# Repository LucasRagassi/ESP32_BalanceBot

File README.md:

# ESP32 BalanceBot V1

Base segura para o BalanceBot de aproximadamente 30 cm, com ESP32 DevKit/WROOM-32 a confirmar, MPU6050, dois motores de passo Creality 42-34 BJ42D15-26V12, cada um com um TMC2209 independente. Estrutura impressa em 3D e PCB KiCad são requisitos do projeto; consulte [CAD_REQUIREMENTS.md](./CAD_REQUIREMENTS.md) e [PCB_REQUIREMENTS.md](./PCB_REQUIREMENTS.md).

**Fase atual: simulação e arquitetura; nenhuma saída STEP/DIR ou driver físico é inicializado ou habilitado.** Valores elétricos dos motores e módulos permanecem pendentes de datasheet/medição. `esp32dev` é só o alvo genérico para compilar e não comprova qual DevKit está conectado.

## Arquitetura

- `include/balance` e `src`: PID de equilíbrio, filtro complementar, estado seguro, validação/persistência NVS, interfaces StepPulseEngine/StepperDriver, rampas de aceleração independentes e monitor de passos perdidos.
- `src/esp32_rmt_step_pulse.cpp`: backend de pulsos RMT para ESP32 isolado por interface. Não é instanciado pelo firmware V1. `src/esp32_app.cpp` usa somente modelos de motor em RAM; o PID de 200 Hz produz demandas limitadas/rampadas simuladas.
- `StepperMotorConfig` de cada lado inclui limite de corrente, sentido, velocidade máxima em steps/s e aceleração em steps/s². Os limites de software são genéricos e conservadores, não substituem o limite seguro do conjunto motor/módulo/PCB.
- A configuração WebSocket é validada na tarefa de controle, aplicada aos simuladores e persistida pela tarefa principal, fora do caminho crítico. Valores de corrente são guardados mas ainda **não são enviados por UART aos TMC2209**.
- A tarefa de controle solicita período de 5 ms, registra execução, jitter, deadlines e desativa os modelos ao entrar em falha. Não faz rede, LittleFS ou NVS.
- Encoders físicos ainda não foram especificados. A perda de passos exibida/testada é exclusivamente simulada; não existe detecção física de posição nesta versão.

## Build e testes

Instale PlatformIO Core e execute na raiz:

```sh
pio run -e native
pio test -e native
pio run -e esp32dev
pio run -e esp32dev -t buildfs
```

Para hardware, somente depois da revisão elétrica e mecânica: `pio run -e esp32dev -t uploadfs`, `pio run -e esp32dev -t upload` e `pio device monitor -b 115200`. Upload físico não foi executado.

Os testes nativos cobrem PID e configuração, estados/falhas, comandos remotos, rampas distintas por eixo, sentido/limites de motor, detecção simulada de passos perdidos e falhas. Build e resultados mais recentes estão em “Validação registrada”.

## Wi-Fi e painel

**Fase 1.4.3 — SoftAP:** `status` agora compara eventos e driver reais (modo/configuração, canal, BSSID, clientes e scans). IP 192.168.4.1 ou sucesso no boot não comprovam beacons RF. Não há restart automático; a causa do desaparecimento em repouso segue dependente de captura física. Veja [DIAGNOSTICO_SOFTAP.md](./DIAGNOSTICO_SOFTAP.md). O scan continua manual/autenticado e exige intervalo mínimo de 15 s.

**Fase 1.4.7 — configuração de rede simplificada:** no Android conectado ao AP `BalanceBot-Setup`, abra `http://192.168.4.1/network`, preencha SSID/senha do roteador **2,4 GHz** e toque **Conectar e salvar**. Não há token, login, cookies ou sessões administrativas. Depois de obter DHCP válido, o ESP32 salva e verifica automaticamente a configuração em NVS `bb_wifi`; falhas preservam a configuração anterior. O portal mostra o IP STA para acesso pelo Fedora na mesma LAN e mantém os campos/foco durante as consultas. O reboot recupera a configuração gravada e reconecta.

**Use somente em rede confiável:** qualquer cliente com acesso ao AP ou à LAN pode consultar/alterar a rede. A senha WPA2 e o IP `192.168.4.1/24` do AP foram preservados. HTTP não cifra a senha STA em trânsito; ela não é devolvida em JSON/telemetria/logs. Não publique as portas 80/81 na Internet. A configuração de rede não concede autorização para acionar motores: DEMO, intertravamentos e motores físicos desabilitados permanecem. Veja [REDE_AP_STA.md](./REDE_AP_STA.md) para arquitetura, testes e limitações.

**Console:** NORMAL continua padrão. Use `pio device monitor -b 115200`, comandos `status`, `help` e `log quiet|normal|debug`. O comando `admin` e a geração/validação de token foram removidos; QR administrativo das fases anteriores não é necessário. Falhas críticas, FAULT e watchdog continuam visíveis.

O link **Diagnóstico** abre `/diagnostics`, uma página responsiva de consulta que atualiza os indicadores a partir da API JSON `/health`. Ela não ocupa a conexão WebSocket do controlador. Seus arquivos `diagnostics.html`, `diagnostics.css` e `diagnostics.js` devem acompanhar o upload manual do LittleFS. Em falhas de consulta, a página sinaliza os dados desatualizados. Consulte [DIAGNOSTICO_HTTP.md](./DIAGNOSTICO_HTTP.md) para testes e instruções de gravação.

Depois de gravar firmware e filesystem, conecte ao AP `BalanceBot-Setup` (senha padrão `BalanceBot123`) e abra `http://192.168.4.1/`. Altere a senha antes de qualquer ensaio. É possível substituir credenciais com `BALANCEBOT_AP_SSID` e `BALANCEBOT_AP_PASSWORD` em `build_flags`.

Para diagnosticar acesso pelo Android, abra primeiro `http://192.168.4.1/health`. Este endpoint não usa LittleFS e retorna JSON com estado do AP/HTTP/WebSocket/tarefa, disponibilidade da IMU, heap e razão de reset. Se LittleFS não estiver montado, `/` ainda responde com uma página HTML curta de diagnóstico; os recursos completos podem exigir `pio run -e esp32dev -t uploadfs`. Prefira digitar o endereço HTTP explícito e desative temporariamente a troca automática para dados móveis/rede sem internet, caso o Android abandone o AP.

O painel expõe perfis independentes por motor. Corrente 0 indica não configurada; configure-a somente após validar corrente de fase/RMS, Rsense e dissipação para os módulos reais. Um cliente WebSocket controlador é aceito; perda de conexão/timeout zera a referência remota, sem desabilitar abruptamente o laço de equilíbrio. A configuração de motor pode ser alterada apenas fora de `EQUILIBRANDO`.

## Estados e segurança

`DESARMADO → CALIBRANDO → PRONTO → EQUILIBRANDO`; falhas latched levam a `FALHA`. Com a MPU6050 ausente no boot, o sistema entra em `DEMO`, permanece servindo a interface e não aceita armamento. A detecção inicial ocorre uma vez; tentativas de recuperação são separadas por 5 s e não há leituras I2C a cada ciclo enquanto o sensor estiver ausente. Se a IMU falhar durante equilíbrio, o controle entra em falha e os modelos são desabilitados. A detecção posterior do sensor não rearma automaticamente: requer reinicialização deliberada. São também tratados atraso de controle, inclinação excessiva, intertravamento aberto e divergência de passos simulada.

**Não conecte motores aos pinos STEP/DIR e não use este firmware para equilibrar fisicamente o robô.** Antes de uma futura habilitação, é obrigatório um E-stop que corte a potência independentemente do software e hardware que mantenha ENN dos dois TMC2209 inativo no boot/reset/brownout. Consulte [HARDWARE.md](./HARDWARE.md).

## Diagnóstico do boot e concorrência

Em 115200 baud, NORMAL exibe um resumo organizado e transições importantes; `status` repete o estado. Em DEBUG, as etapas registram início/resultado, timestamp monotônico, heap e NVS/defaults; o loop e a tarefa produzem diagnósticos de heartbeat/watermark a cada 10 s, impressos pelo loop por filas não bloqueantes. Esses diagnósticos periódicos não aparecem em NORMAL/QUIET. Watermark abaixo de 256 unidades gera alerta crítico em qualquer nível. A razão de reset aparece no resumo; resets panic/watchdog/brownout geram aviso crítico. O loop continua atendendo HTTP/WS e não há limpeza automática de NVS.

Não há espera infinita explícita: as filas usam timeout zero, o controle usa `vTaskDelayUntil` em 5 ms e o I2C tem timeout de 20 ms. O snapshot protege apenas a cópia curta por seção crítica/mutex RAII; a persistência NVS ocorre no loop, fora da tarefa de controle. Diagnóstico de watermark não substitui um ensaio prolongado nem prova ausência de stack overflow/deadlock em hardware.

## Validação registrada

Execução local em 27/10/2026, PlatformIO Core 6.2.0:

| Comando | Resultado |
|---|---|
| `pio run -e native` | Sucesso |
| `pio test -e native` | Sucesso — 38/38 casos Unity (Fase 1.4.3) |
| `pio run -e esp32dev` | Sucesso — firmware, incluindo backend RMT compilado |
| `pio run -e esp32dev -t buildfs` | Sucesso — painel V1 empacotado |

O AP, o barramento MPU6050 e as formas de onda RMT não foram testados em placa física. A variante do módulo, correntes, pinagem real dos módulos TMC2209, Rsense e características elétricas dos dois motores permanecem pendentes.

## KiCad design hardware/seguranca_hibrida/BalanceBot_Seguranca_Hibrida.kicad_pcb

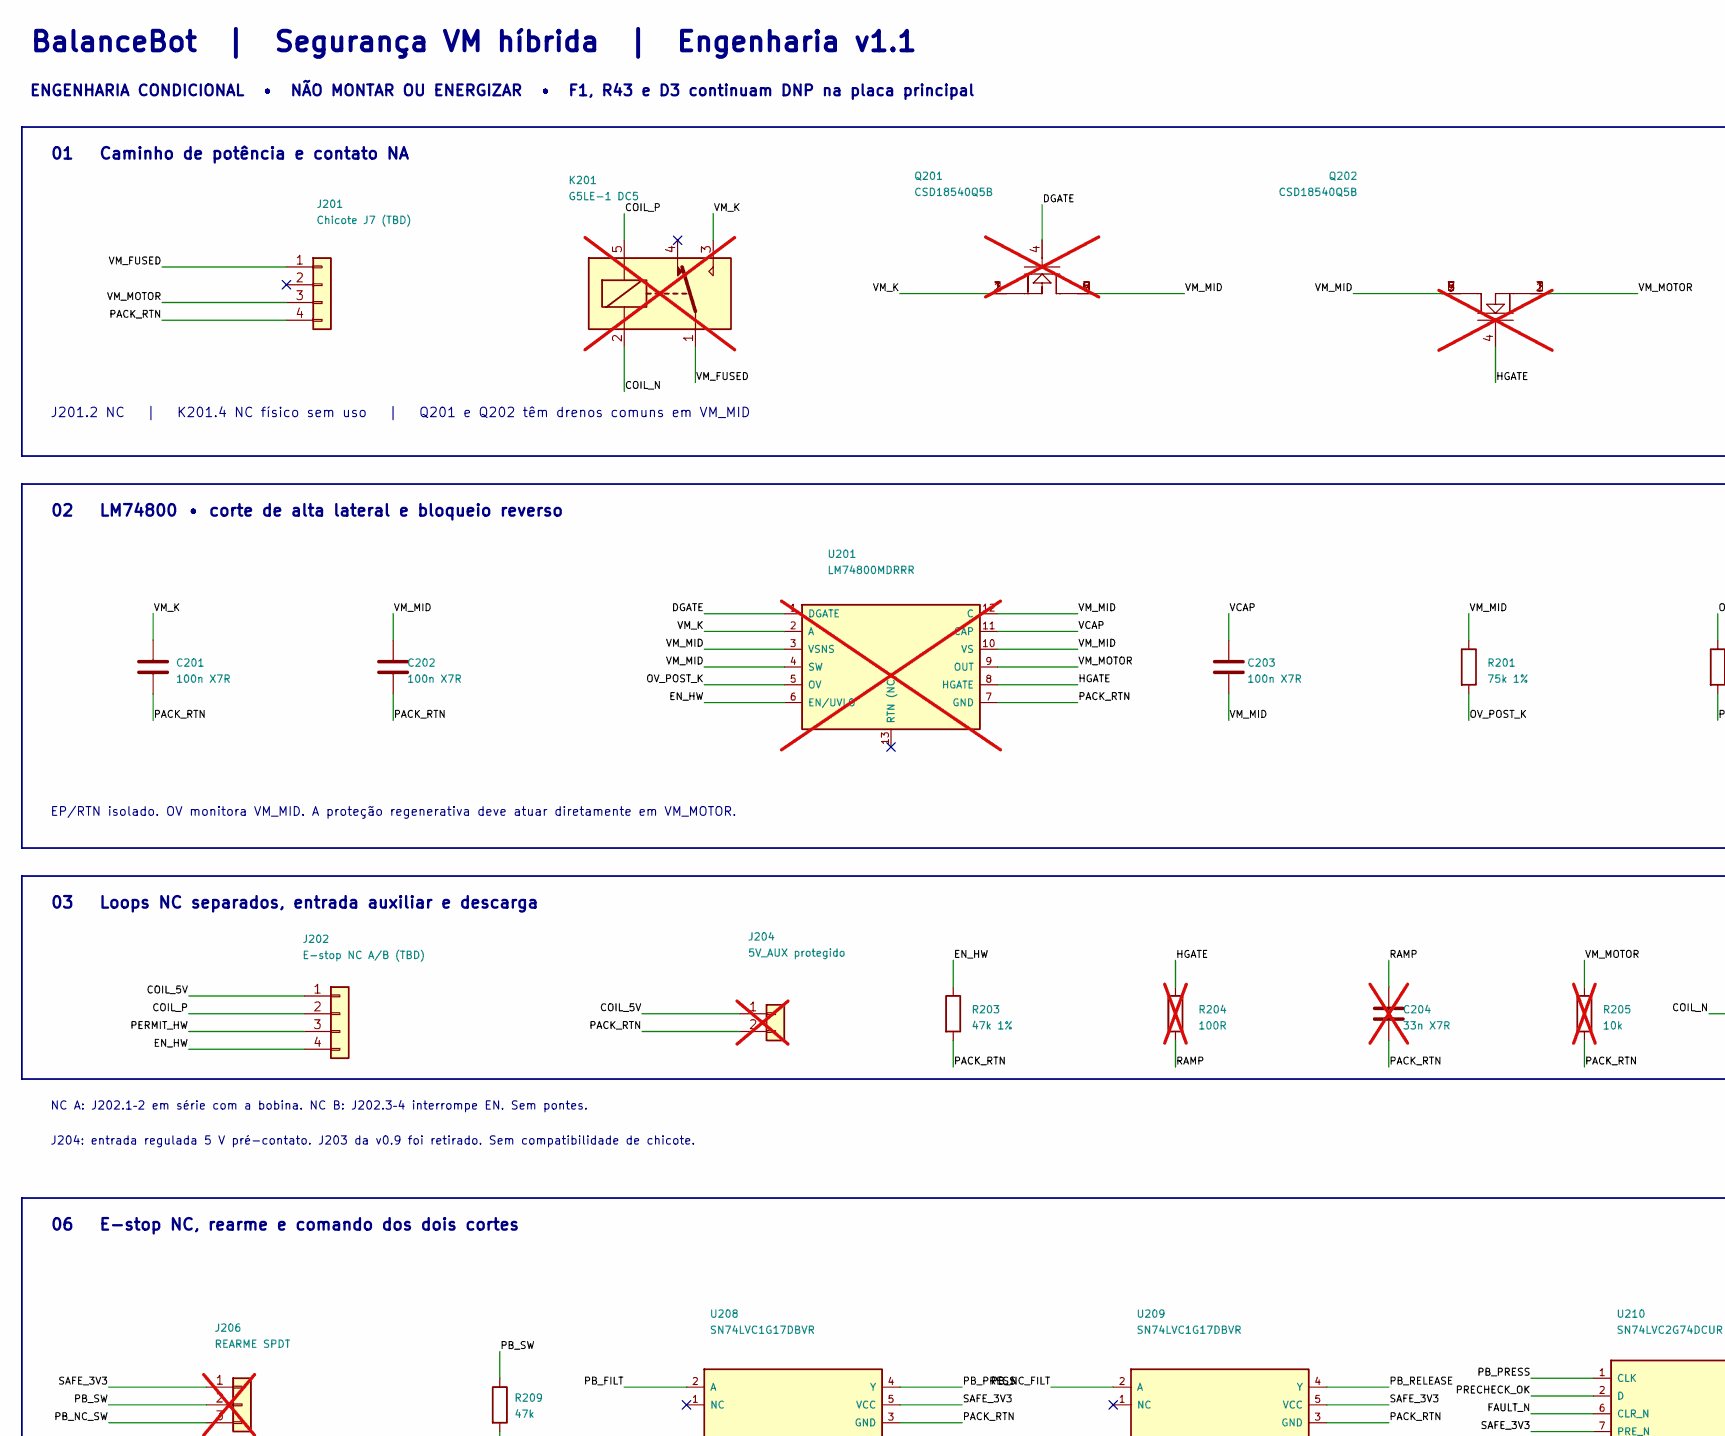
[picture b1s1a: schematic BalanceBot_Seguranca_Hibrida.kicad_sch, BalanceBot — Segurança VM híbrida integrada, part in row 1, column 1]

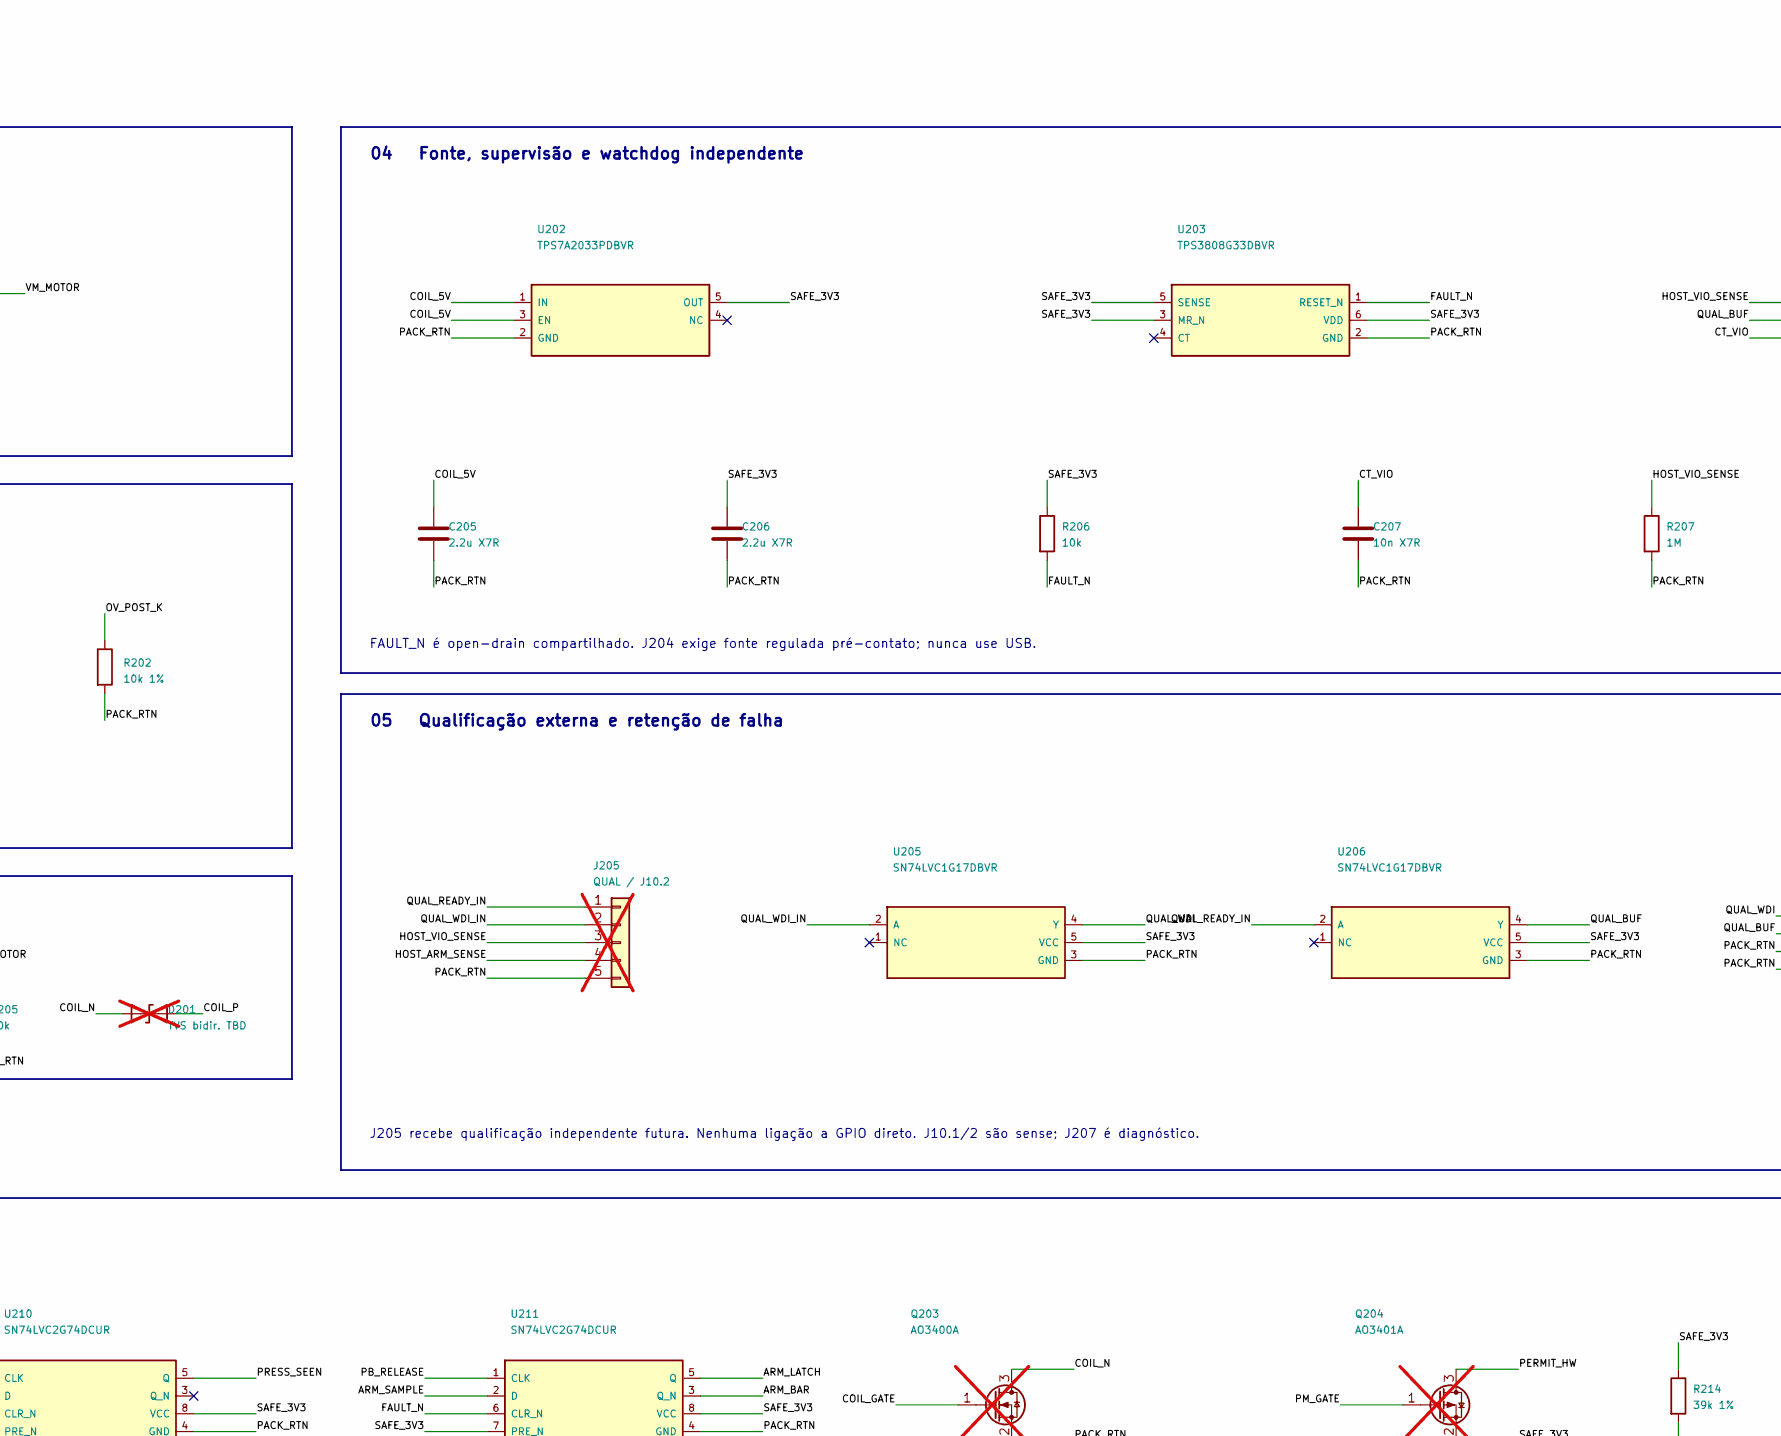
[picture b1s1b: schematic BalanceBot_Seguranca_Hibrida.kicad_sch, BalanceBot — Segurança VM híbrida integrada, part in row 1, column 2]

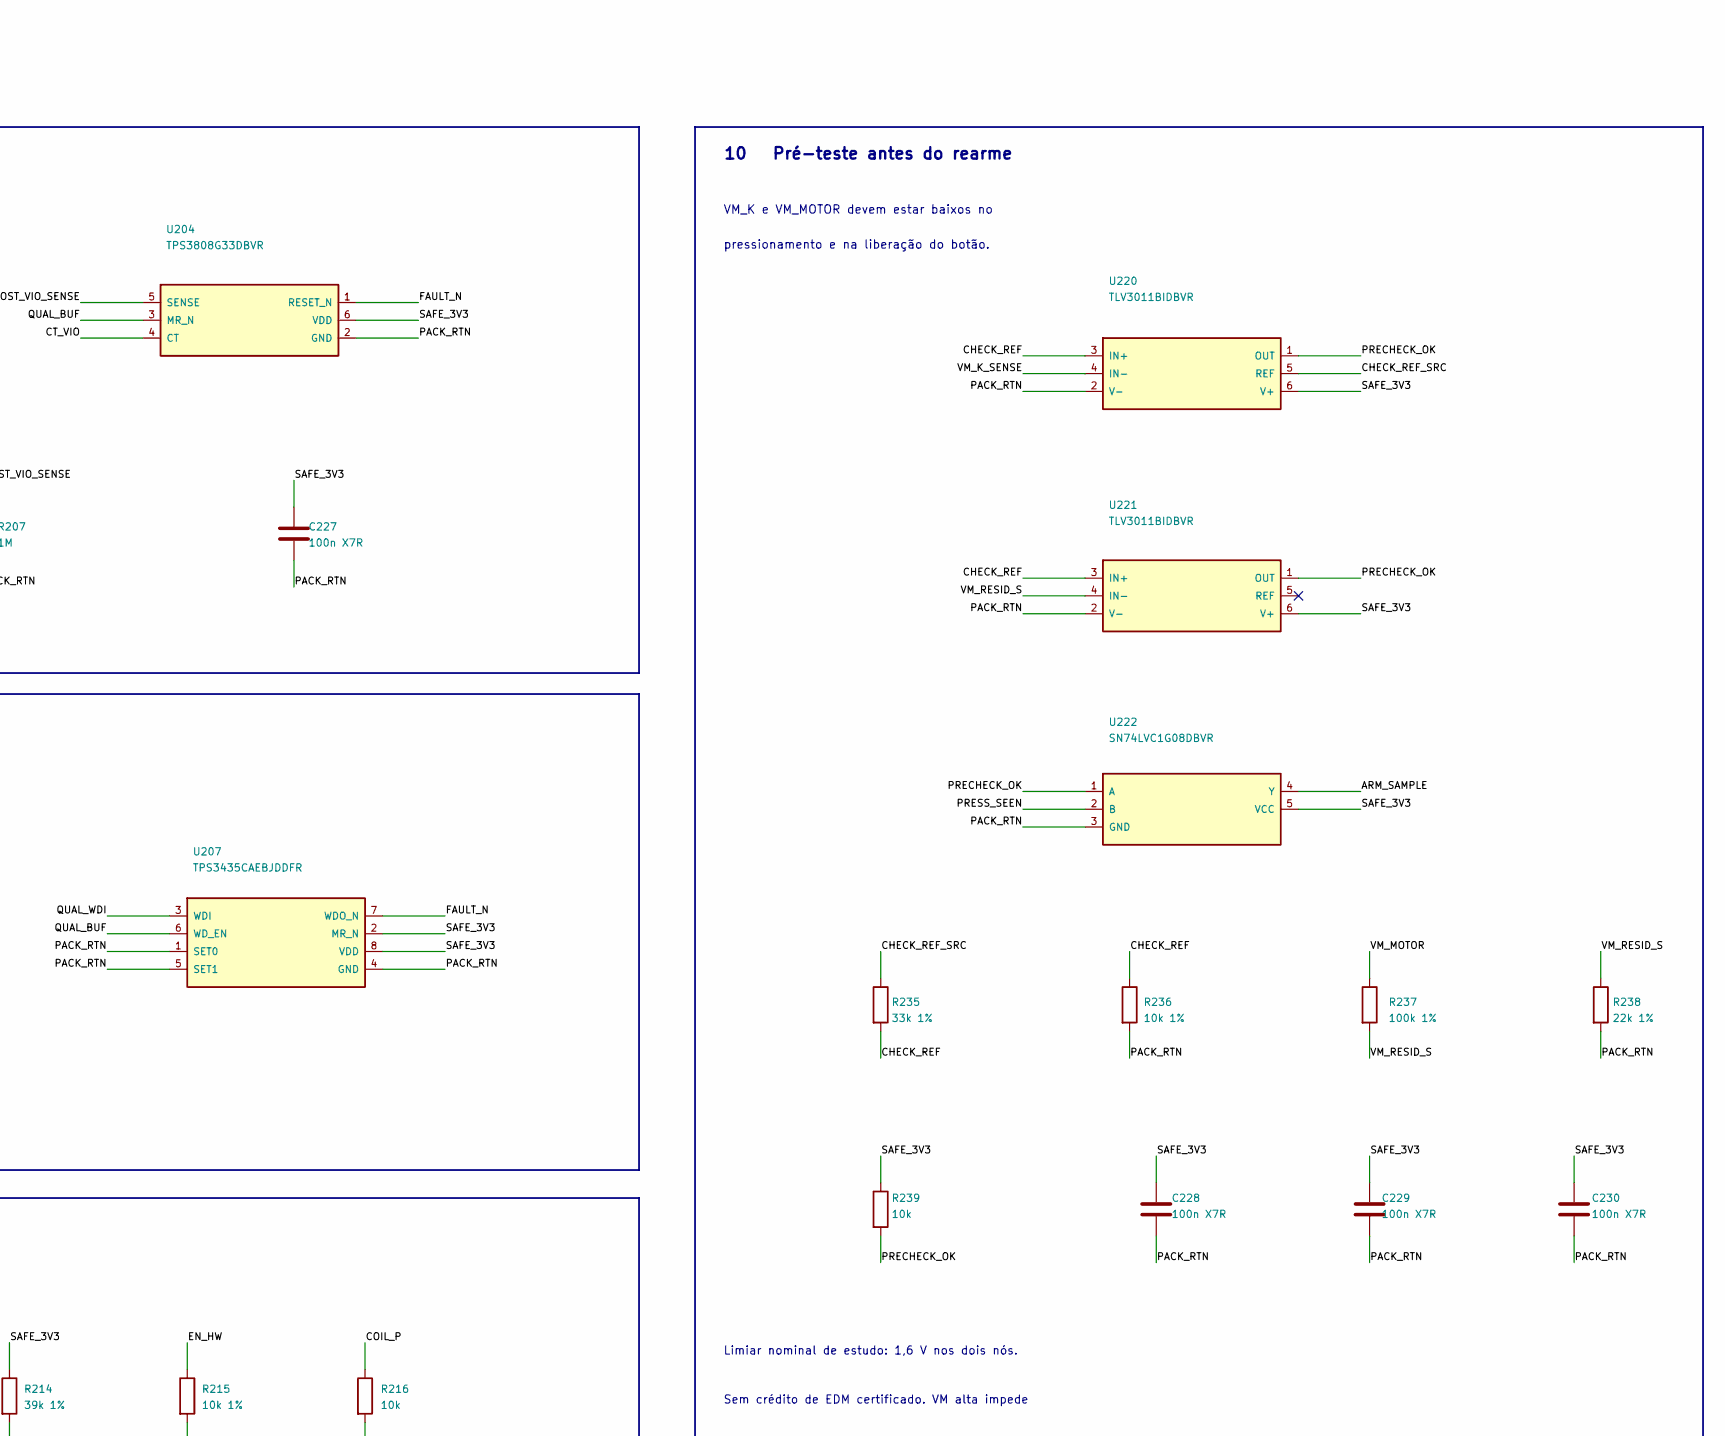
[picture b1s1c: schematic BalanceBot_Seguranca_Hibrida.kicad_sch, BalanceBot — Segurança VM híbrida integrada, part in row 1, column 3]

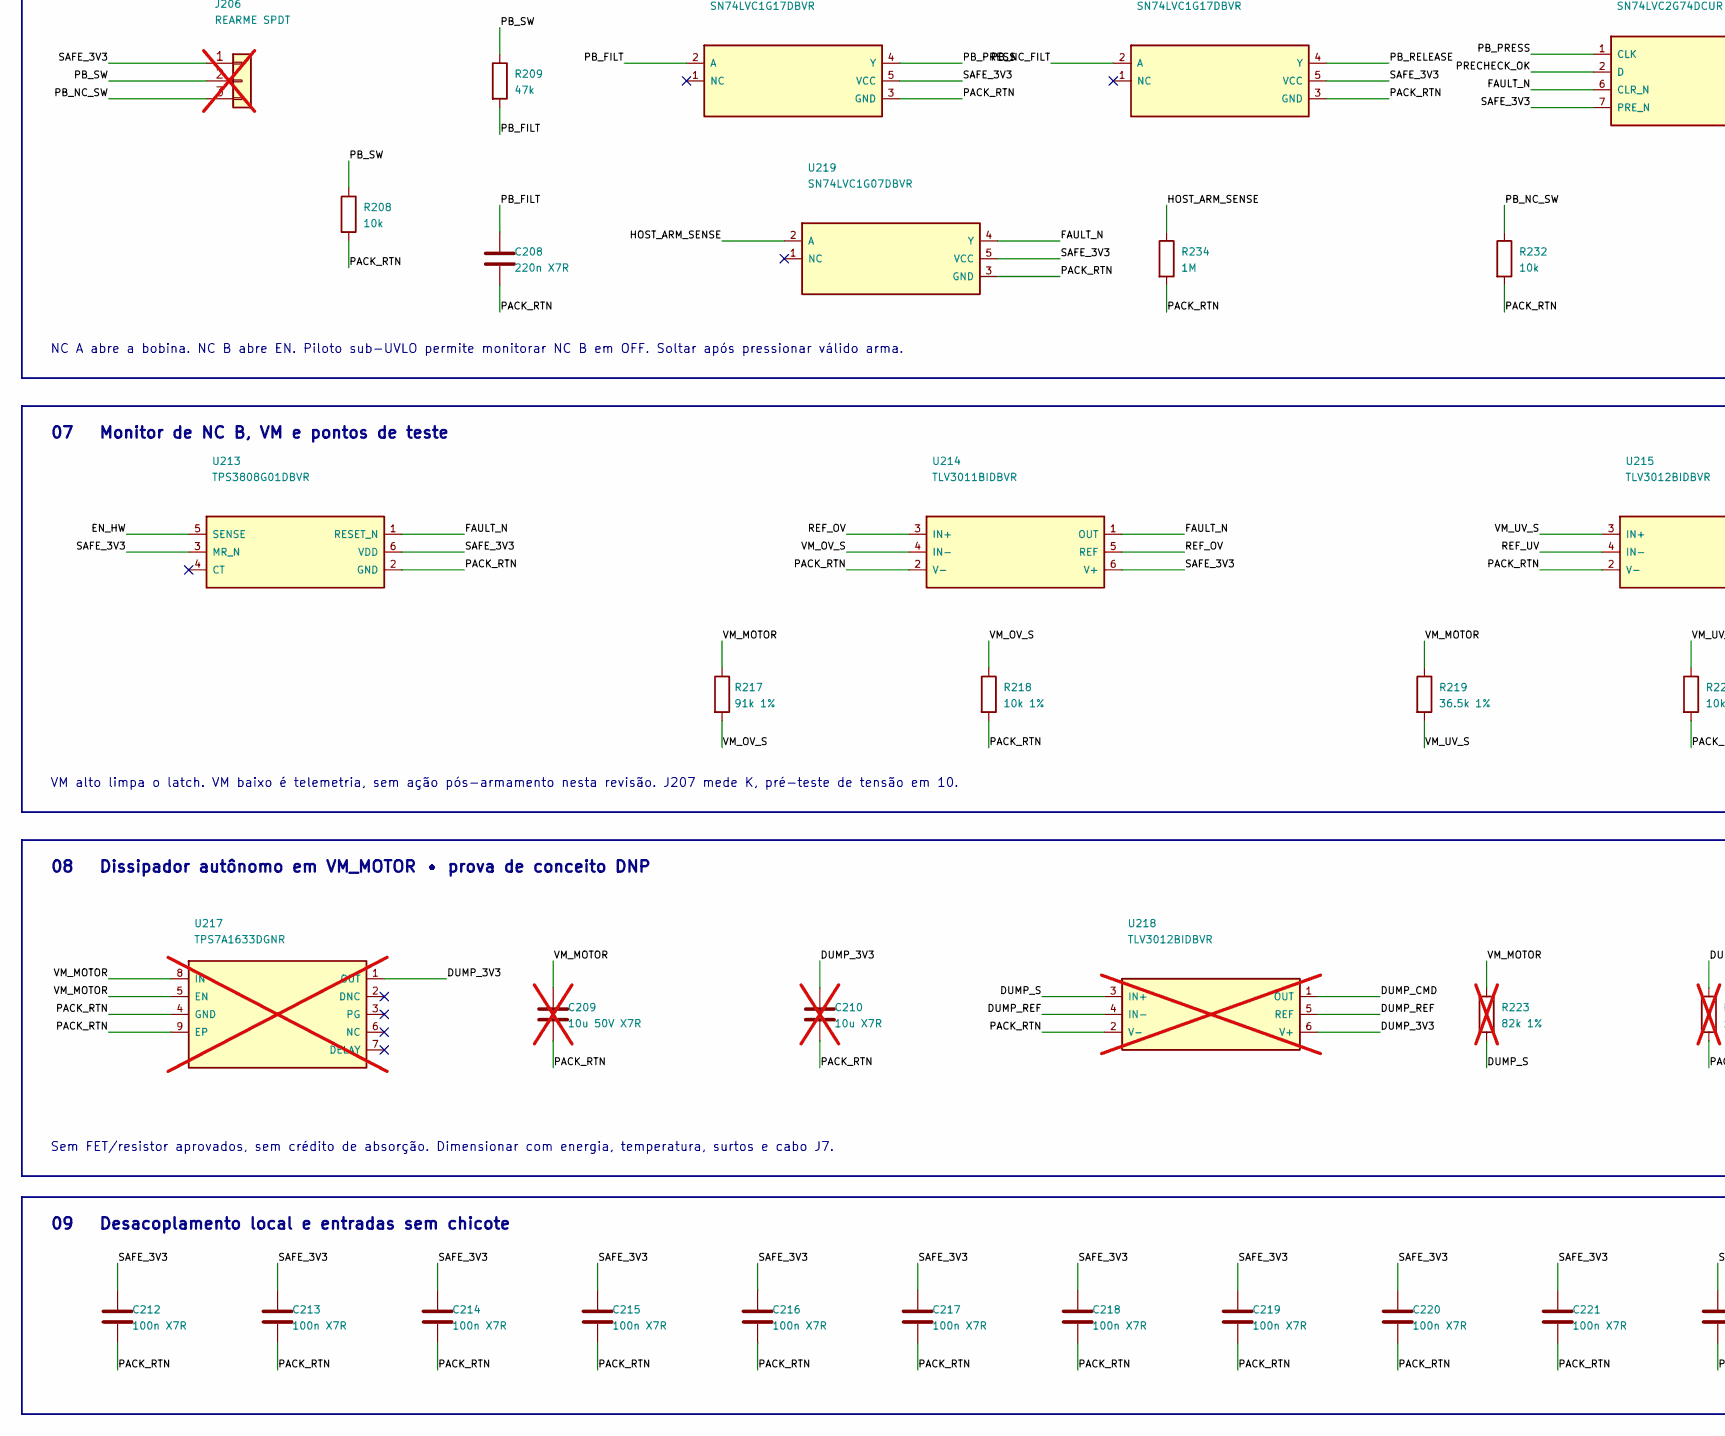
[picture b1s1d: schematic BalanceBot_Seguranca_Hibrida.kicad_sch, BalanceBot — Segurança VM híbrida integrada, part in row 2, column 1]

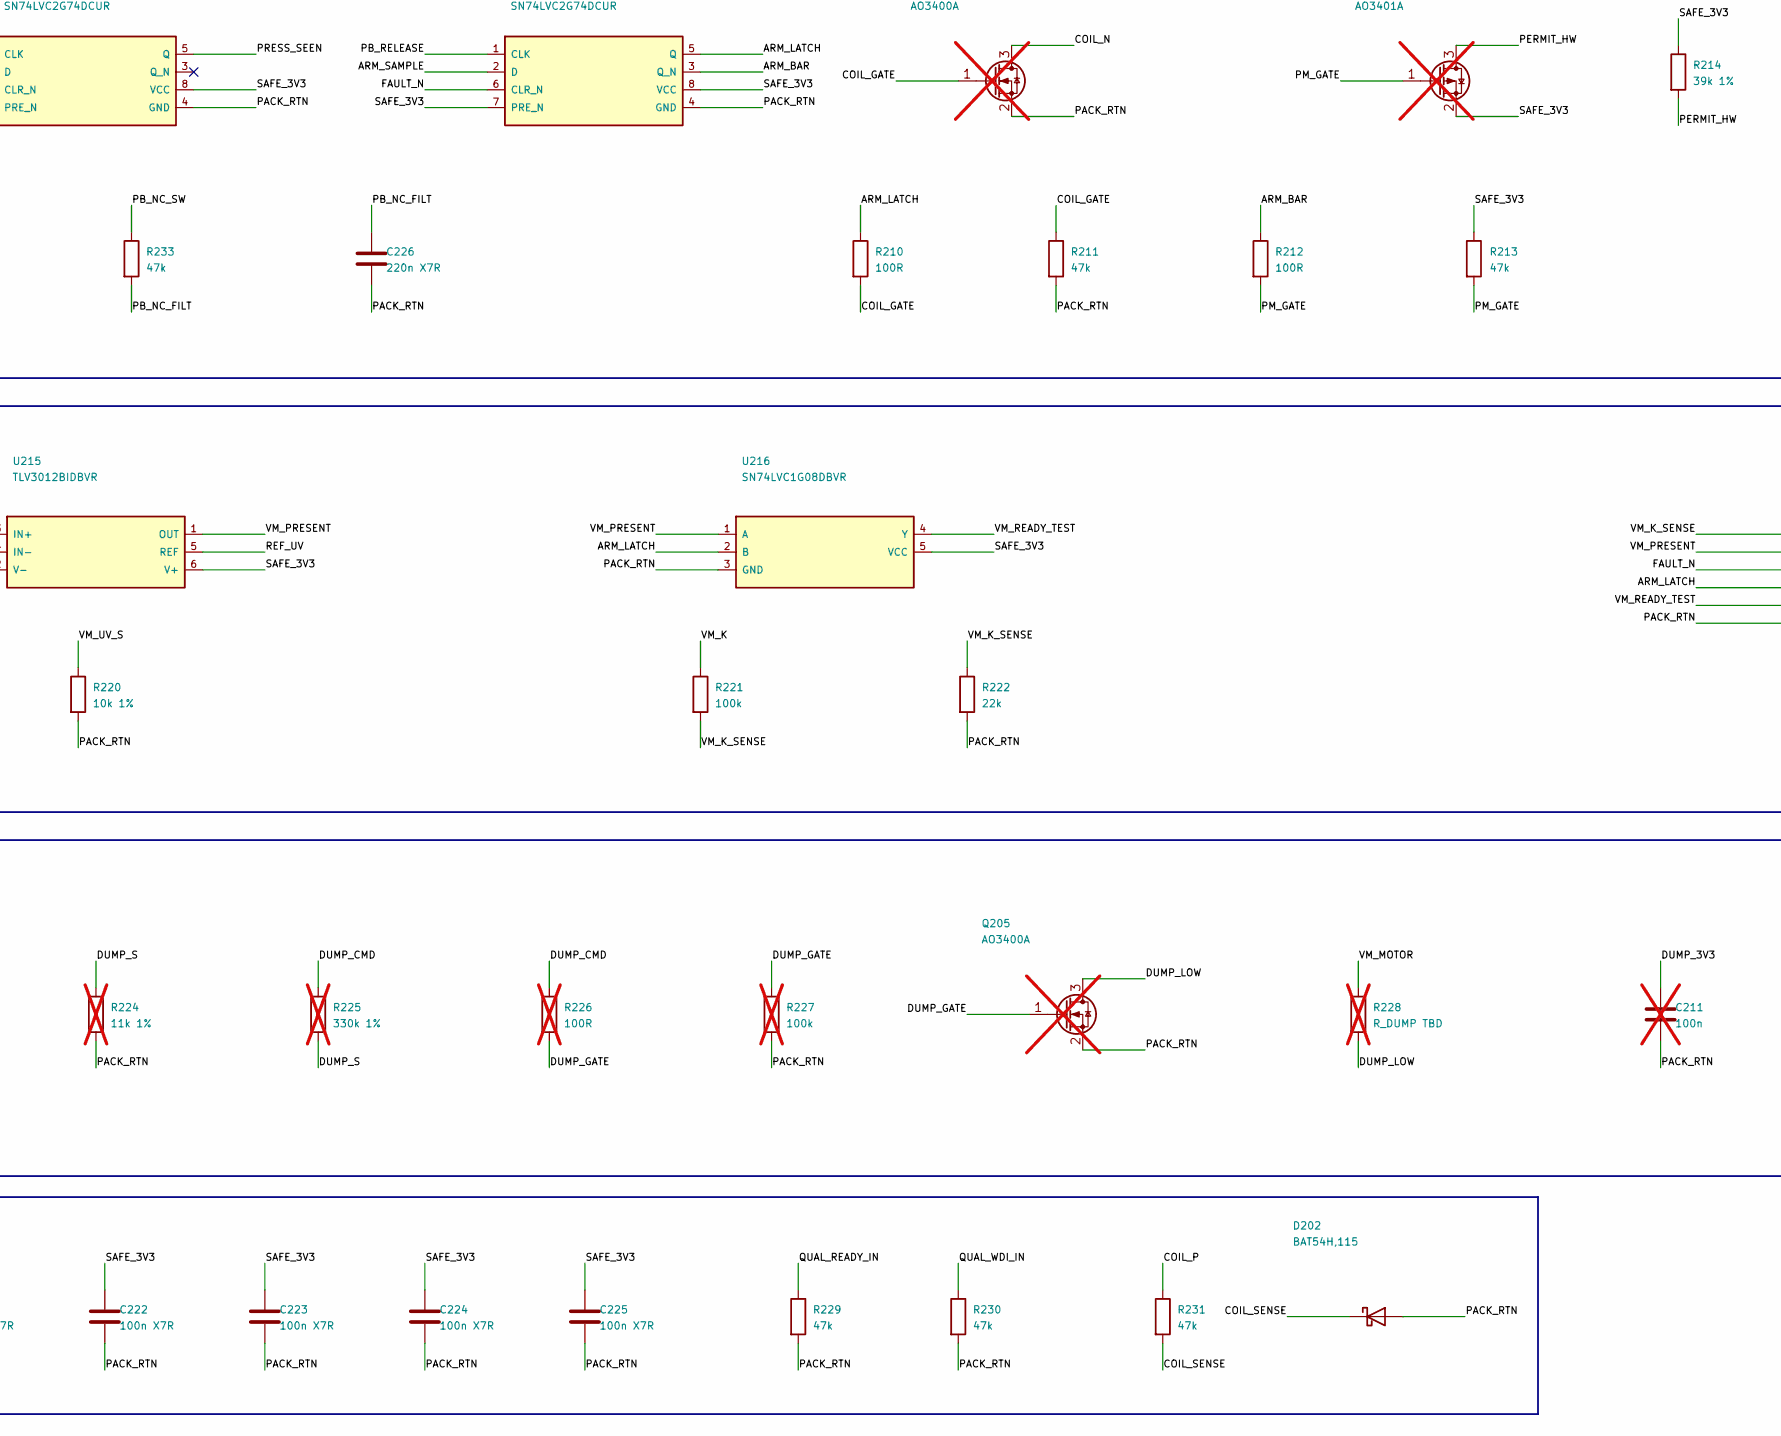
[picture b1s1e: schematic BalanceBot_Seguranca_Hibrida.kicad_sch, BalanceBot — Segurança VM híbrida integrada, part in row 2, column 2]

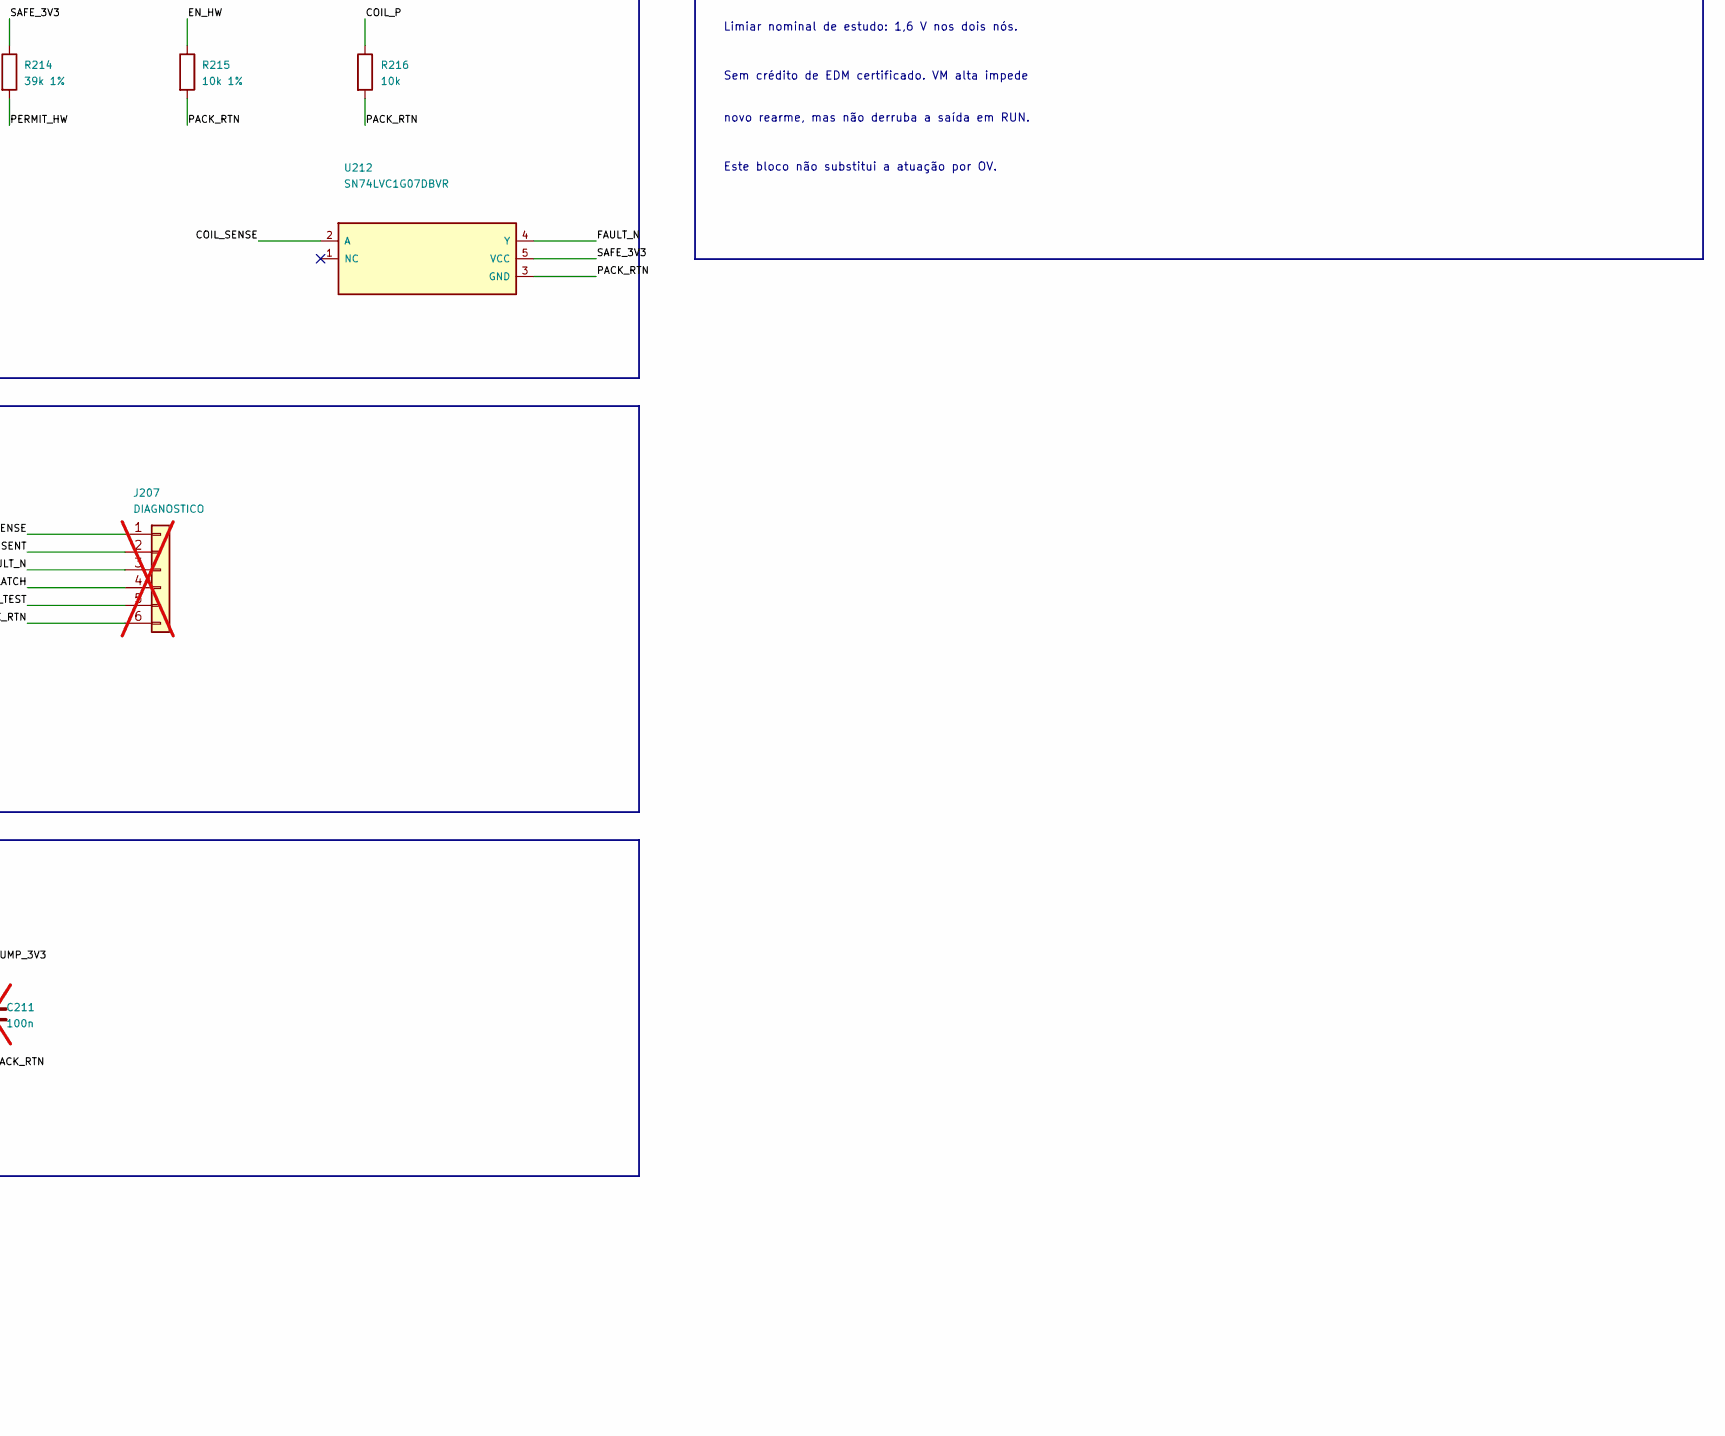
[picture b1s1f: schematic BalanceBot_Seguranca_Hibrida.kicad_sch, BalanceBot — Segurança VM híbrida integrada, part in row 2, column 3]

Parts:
C201, C202, C203, C212, C213, C214, C215, C216, C217, C218, C219, C220, C221, C222, C223, C224, C225, C227, C228, C229, C230: 100n X7R; C_0603_1608Metric
C204: 33n X7R; C_0603_1608Metric; not fitted
C205, C206: 2.2u X7R; C_0805_2012Metric
C207: 10n X7R; C_0603_1608Metric
C208, C226: 220n X7R; C_0603_1608Metric
C209: 10u 50V X7R; C_1206_3216Metric; not fitted
C210: 10u X7R; C_0805_2012Metric; not fitted
C211: 100n; C_0603_1608Metric; not fitted
D201: TVS bidir. TBD; D_SMB; not fitted
D202: BAT54H,115; D_SOD-123F
J201: Chicote J7 (TBD)
J202: E-stop NC A/B (TBD)
J204: 5V_AUX protegido; not fitted
J205: QUAL / J10.2; not fitted
J206: REARME SPDT; not fitted
J207: DIAGNOSTICO; not fitted
K201: G5LE-1 DC5; not fitted
Q201, Q202: CSD18540Q5B; DNK0008A; not fitted
Q203, Q205: AO3400A; SOT-23; not fitted
Q204: AO3401A; SOT-23; not fitted
R201: 75k 1%; R_0603_1608Metric
R202, R215, R218, R220, R236: 10k 1%; R_0603_1608Metric
R203: 47k 1%; R_0603_1608Metric
R204, R226: 100R; R_0603_1608Metric; not fitted
R205: 10k; R_0603_1608Metric; not fitted
R206, R208, R216, R232, R239: 10k; R_0603_1608Metric
R207, R234: 1M; R_0603_1608Metric
R209, R211, R213, R229, R230, R231, R233: 47k; R_0603_1608Metric
R210, R212: 100R; R_0603_1608Metric
R214: 39k 1%; R_0603_1608Metric
R217: 91k 1%; R_0603_1608Metric
R219: 36.5k 1%; R_0603_1608Metric
R221: 100k; R_0603_1608Metric
R222: 22k; R_0603_1608Metric
R223: 82k 1%; R_0603_1608Metric; not fitted
R224: 11k 1%; R_0603_1608Metric; not fitted
R225: 330k 1%; R_0603_1608Metric; not fitted
R227: 100k; R_0603_1608Metric; not fitted
R228: R_DUMP TBD; not fitted
R235: 33k 1%; R_0603_1608Metric
R237: 100k 1%; R_0603_1608Metric
R238: 22k 1%; R_0603_1608Metric
U201: LM74800MDRRR; DRR0012E; not fitted
U202: TPS7A2033PDBVR; SOT-23-5
U203, U204: TPS3808G33DBVR; SOT-23-6
U205, U206, U208, U209: SN74LVC1G17DBVR; SOT-23-5
U207: TPS3435CAEBJDDFR; TI_DDF0008A_TPS3435
U210, U211: SN74LVC2G74DCUR; TI_DCU0008A_SN74LVC2G74
U212, U219: SN74LVC1G07DBVR; SOT-23-5
U213: TPS3808G01DBVR; SOT-23-6
U214, U220, U221: TLV3011BIDBVR; SOT-23-6
U215: TLV3012BIDBVR; SOT-23-6
U216, U222: SN74LVC1G08DBVR; SOT-23-5
U217: TPS7A1633DGNR; TI_DGN0008C_TPS7A16; not fitted
U218: TLV3012BIDBVR; SOT-23-6; not fitted

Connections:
/ARM_BAR: R212.1, U211.3 (Q_N)
/ARM_LATCH: J207.4, R210.1, U211.5 (Q), U216.2 (B)
/ARM_SAMPLE: U211.2 (D), U222.4 (Y)
/CHECK_REF: R235.2, R236.1, U220.3 (IN+), U221.3 (IN+)
/CHECK_REF_SRC: R235.1, U220.5 (REF)
/COIL_5V: C205.1, J202.1, J204.1, U202.1 (IN), U202.3 (EN)
/COIL_GATE: Q203.1 (G), R210.2, R211.1
/COIL_N: D201.1 (A1), K201.2, Q203.3 (D)
/COIL_P: D201.2 (A2), J202.2, K201.5, R216.1, R231.1
/COIL_SENSE: D202.1 (K), R231.2, U212.2 (A)
/CT_VIO: C207.1, U204.4 (CT)
/DGATE: Q201.4 (Gate), U201.1 (DGATE)
/DUMP_3V3: C210.1, C211.1, U217.1 (OUT), U218.6 (V+)
/DUMP_CMD: R225.1, R226.1, U218.1 (OUT)
/DUMP_GATE: Q205.1 (G), R226.2, R227.1
/DUMP_LOW: Q205.3 (D), R228.2
/DUMP_REF: U218.4 (IN-), U218.5 (REF)
/DUMP_S: R223.2, R224.1, R225.2, U218.3 (IN+)
/EN_HW: J202.4, R203.1, R215.1, U201.6 (EN/UVLO), U213.5 (SENSE)
/FAULT_N: J207.3, R206.2, U203.1 (RESET_N), U204.1 (RESET_N), U207.7 (WDO_N), U210.6 (CLR_N), U211.6 (CLR_N), U212.4 (Y), U213.1 (RESET_N), U214.1 (OUT), U219.4 (Y)
/HGATE: Q202.4 (Gate), R204.1, U201.8 (HGATE)
/HOST_ARM_SENSE: J205.4, R234.1, U219.2 (A)
/HOST_VIO_SENSE: J205.3, R207.1, U204.5 (SENSE)
/OV_POST_K: R201.2, R202.1, U201.5 (OV)
/PACK_RTN: C201.2, C202.2, C204.2, C205.2, C206.2, C207.2, C208.2, C209.2, C210.2, C211.2, C212.2, C213.2, C214.2, C215.2, C216.2, C217.2, C218.2, C219.2, C220.2, C221.2, C222.2, C223.2, C224.2, C225.2, C226.2, C227.2, C228.2, C229.2, C230.2, D202.2 (A), J201.4, J204.2, J205.5, J207.6, Q203.2 (S), Q205.2 (S), R202.2, R203.2, R205.2, R207.2, R208.2, R211.2, R215.2, R216.2, R218.2, R220.2, R222.2, R224.2, R227.2, R229.2, R230.2, R232.2, R234.2, R236.2, R238.2, U201.7 (GND), U202.2 (GND), U203.2 (GND), U204.2 (GND), U205.3 (GND), U206.3 (GND), U207.1 (SET0), U207.4 (GND), U207.5 (SET1), U208.3 (GND), U209.3 (GND), U210.4 (GND), U211.4 (GND), U212.3 (GND), U213.2 (GND), U214.2 (V-), U215.2 (V-), U216.3 (GND), U217.4 (GND), U217.9 (EP), U218.2 (V-), U219.3 (GND), U220.2 (V-), U221.2 (V-), U222.3 (GND)
/PB_FILT: C208.1, R209.2, U208.2 (A)
/PB_NC_FILT: C226.1, R233.2, U209.2 (A)
/PB_NC_SW: J206.3, R232.1, R233.1
/PB_PRESS: U208.4 (Y), U210.1 (CLK)
/PB_RELEASE: U209.4 (Y), U211.1 (CLK)
/PB_SW: J206.2, R208.1, R209.1
/PERMIT_HW: J202.3, Q204.3 (D), R214.2
/PM_GATE: Q204.1 (G), R212.2, R213.2
/PRECHECK_OK: R239.2, U210.2 (D), U220.1 (OUT), U221.1 (OUT), U222.1 (A)
/PRESS_SEEN: U210.5 (Q), U222.2 (B)
/QUAL_BUF: U204.3 (MR_N), U206.4 (Y), U207.6 (WD_EN)
/QUAL_READY_IN: J205.1, R229.1, U206.2 (A)
/QUAL_WDI: U205.4 (Y), U207.3 (WDI)
/QUAL_WDI_IN: J205.2, R230.1, U205.2 (A)
/RAMP: C204.1, R204.2
/REF_OV: U214.3 (IN+), U214.5 (REF)
/REF_UV: U215.4 (IN-), U215.5 (REF)
/SAFE_3V3: C206.1, C212.1, C213.1, C214.1, C215.1, C216.1, C217.1, C218.1, C219.1, C220.1, C221.1, C222.1, C223.1, C224.1, C225.1, C227.1, C228.1, C229.1, C230.1, J206.1, Q204.2 (S), R206.1, R213.1, R214.1, R239.1, U202.5 (OUT), U203.3 (MR_N), U203.5 (SENSE), U203.6 (VDD), U204.6 (VDD), U205.5 (VCC), U206.5 (VCC), U207.2 (MR_N), U207.8 (VDD), U208.5 (VCC), U209.5 (VCC), U210.7 (PRE_N), U210.8 (VCC), U211.7 (PRE_N), U211.8 (VCC), U212.5 (VCC), U213.3 (MR_N), U213.6 (VDD), U214.6 (V+), U215.6 (V+), U216.5 (VCC), U219.5 (VCC), U220.6 (V+), U221.6 (V+), U222.5 (VCC)
/VCAP: C203.1, U201.11 (CAP)
/VM_K: C201.1, K201.3, Q201.1 (Source), Q201.2 (Source), Q201.3 (Source), R221.1, U201.2 (A)
/VM_K_SENSE: J207.1, R221.2, R222.1, U220.4 (IN-)
/VM_MID: C202.1, C203.2, Q201.5 (Drain), Q201.6 (Drain), Q201.7 (Drain), Q201.8 (Drain), Q201.9 (Drain), Q202.5 (Drain), Q202.6 (Drain), Q202.7 (Drain), Q202.8 (Drain), Q202.9 (Drain), R201.1, U201.3 (VSNS), U201.4 (SW), U201.10 (VS), U201.12 (C)
/VM_MOTOR: C209.1, J201.3, Q202.1 (Source), Q202.2 (Source), Q202.3 (Source), R205.1, R217.1, R219.1, R223.1, R228.1, R237.1, U201.9 (OUT), U217.5 (EN), U217.8 (IN)
/VM_OV_S: R217.2, R218.1, U214.4 (IN-)
/VM_PRESENT: J207.2, U215.1 (OUT), U216.1 (A)
/VM_READY_TEST: J207.5, U216.4 (Y)
/VM_RESID_S: R237.2, R238.1, U221.4 (IN-)
/VM_UV_S: R219.2, R220.1, U215.3 (IN+)
unnamed: J201.1, K201.1

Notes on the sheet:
BalanceBot | Segurança VM híbrida | Engenharia v1.1
ENGENHARIA CONDICIONAL • NÃO MONTAR OU ENERGIZAR • F1, R43 e D3 continuam DNP na placa principal
01 Caminho de potência e contato NA
J201.2 NC | K201.4 NC físico sem uso | Q201 e Q202 têm drenos comuns em VM_MID
02 LM74800 • corte de alta lateral e bloqueio reverso
EP/RTN isolado. OV monitora VM_MID. A proteção regenerativa deve atuar diretamente em VM_MOTOR.
03 Loops NC separados, entrada auxiliar e descarga
NC A: J202.1–2 em série com a bobina. NC B: J202.3–4 interrompe EN. Sem pontes.
J204: entrada regulada 5 V pré-contato. J203 da v0.9 foi retirado. Sem compatibilidade de chicote.
04 Fonte, supervisão e watchdog independente
FAULT_N é open-drain compartilhado. J204 exige fonte regulada pré-contato; nunca use USB.
05 Qualificação externa e retenção de falha
J205 recebe qualificação independente futura. Nenhuma ligação a GPIO direto. J10.1/2 são sense; J207 é diagnóstico.
06 E-stop NC, rearme e comando dos dois cortes
NC A abre a bobina. NC B abre EN. Piloto sub-UVLO permite monitorar NC B em OFF. Soltar após pressionar válido arma.
07 Monitor de NC B, VM e pontos de teste
VM alto limpa o latch. VM baixo é telemetria, sem ação pós-armamento nesta revisão. J207 mede K, pré-teste de tensão em 10.
08 Dissipador autônomo em VM_MOTOR • prova de conceito DNP
Sem FET/resistor aprovados, sem crédito de absorção. Dimensionar com energia, temperatura, surtos e cabo J7.
09 Desacoplamento local e entradas sem chicote
10 Pré-teste antes do rearme
VM_K e VM_MOTOR devem estar baixos no
pressionamento e na liberação do botão.
Limiar nominal de estudo: 1,6 V nos dois nós.
Sem crédito de EDM certificado. VM alta impede
novo rearme, mas não derruba a saída em RUN.
Este bloco não substitui a atuação por OV.

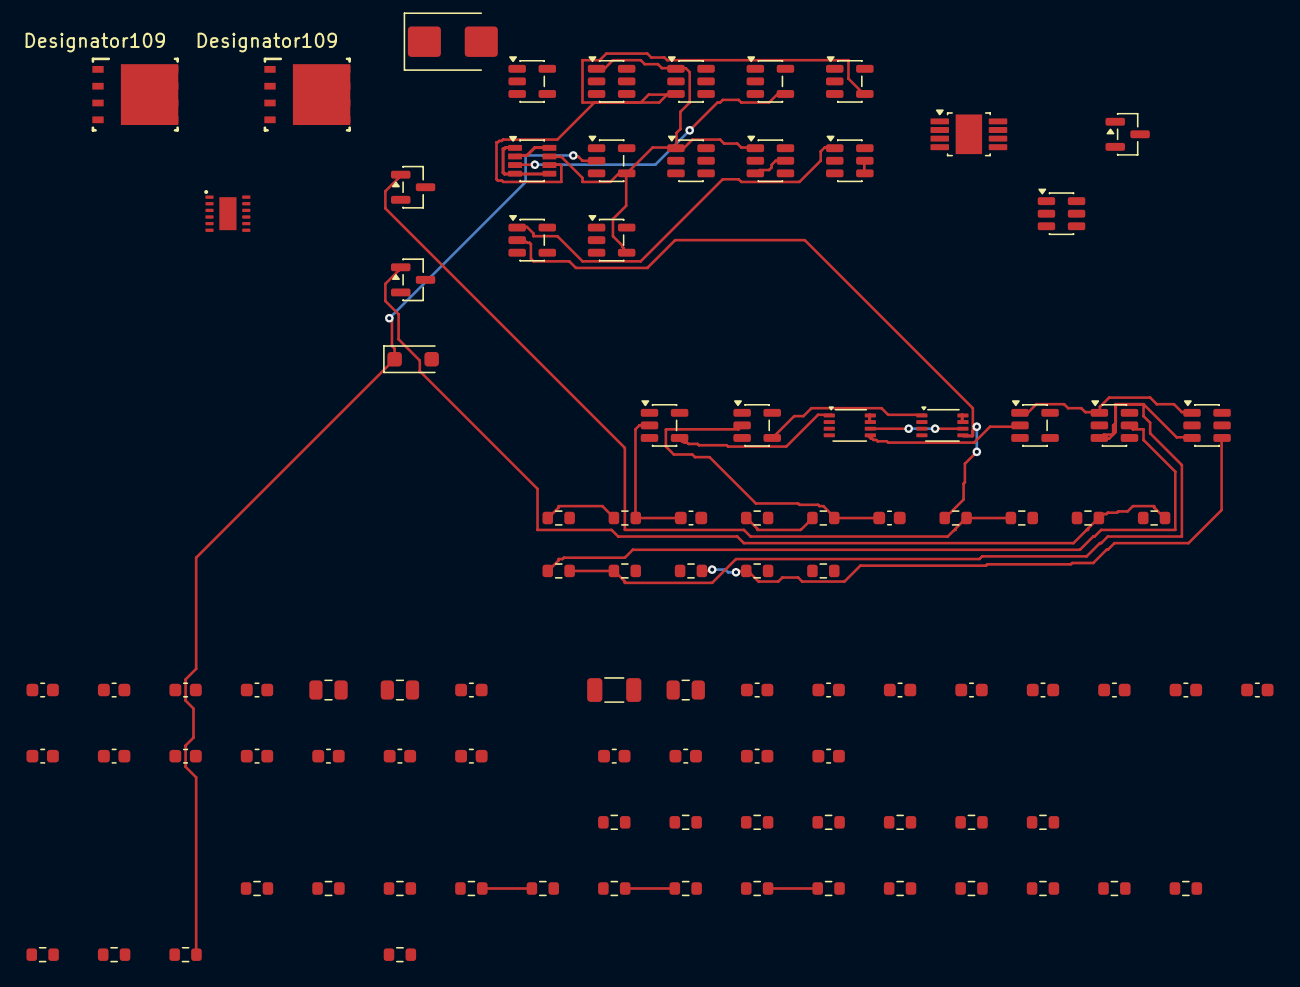
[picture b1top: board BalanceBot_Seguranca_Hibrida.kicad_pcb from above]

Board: 2 copper layers, 97 parts (0 on the bottom side), 51 nets.
